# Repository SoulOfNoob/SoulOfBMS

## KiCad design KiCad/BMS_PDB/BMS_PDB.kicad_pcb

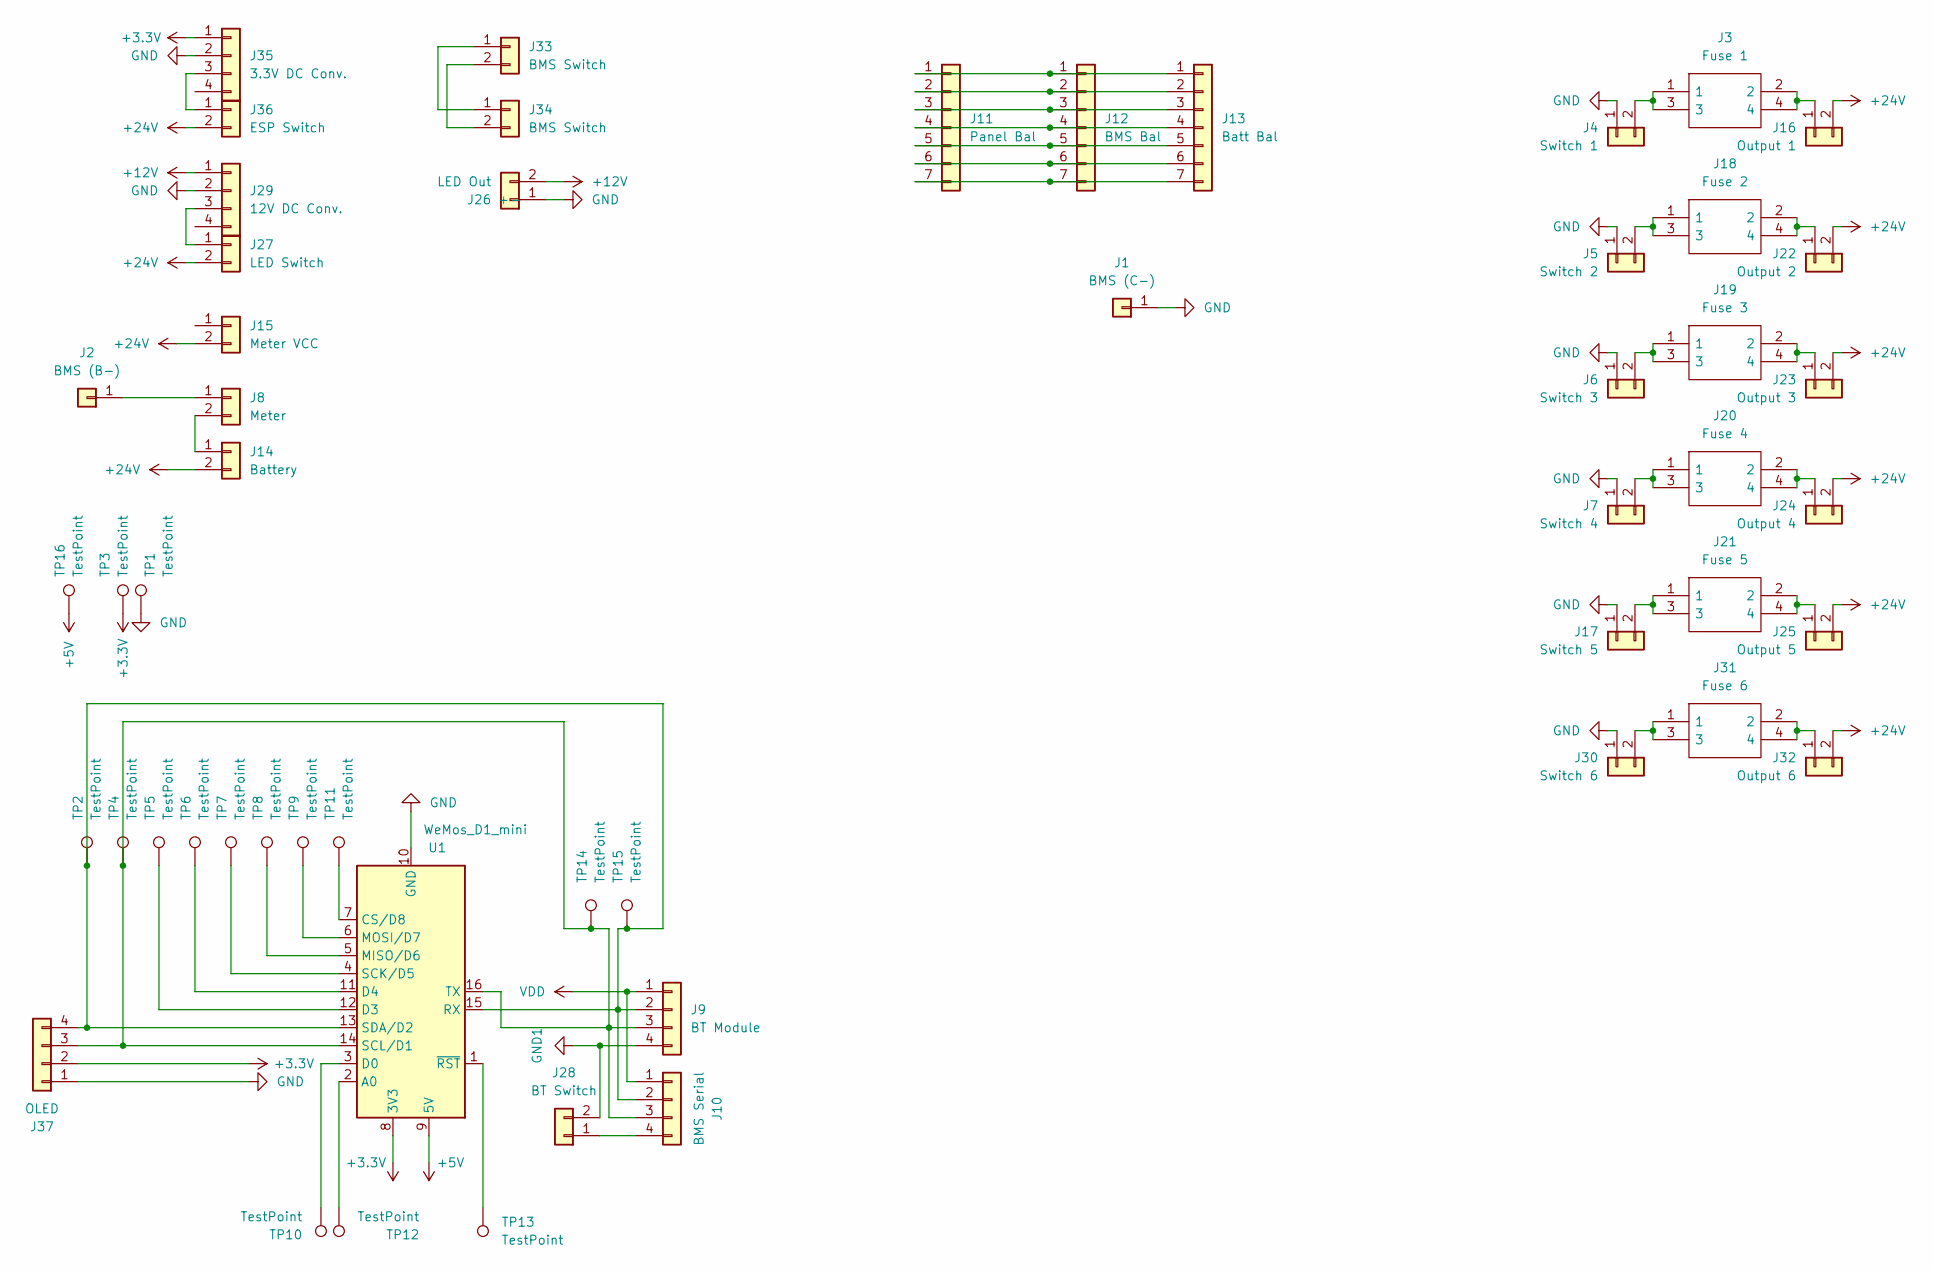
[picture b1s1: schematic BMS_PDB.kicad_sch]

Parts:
J1: BMS (C-); MountingHole_3.5mm_Pad_Via
J2: BMS (B-); MountingHole_3.5mm_Pad_Via
J3: Fuse 1; Fuseholder3557; Mouser Part Number 534-3557-2
J4: Switch 1; AMASS_XT30U-M_1x02_P5.0mm_Vertical_CUSTOM
J5: Switch 2; AMASS_XT30U-M_1x02_P5.0mm_Vertical_CUSTOM
J6: Switch 3; AMASS_XT30U-M_1x02_P5.0mm_Vertical_CUSTOM
J7: Switch 4; AMASS_XT30U-M_1x02_P5.0mm_Vertical_CUSTOM
J8: Meter; AMASS_XT60-M_1x02_P7.20mm_Vertical
J9: BT Module; JST_XH_B4B-XH-A_1x04_P2.50mm_Vertical
J10: BMS Serial; JST_XH_B4B-XH-A_1x04_P2.50mm_Vertical
J11: Panel Bal; JST_XH_B7B-XH-A_1x07_P2.50mm_Vertical
J12: BMS Bal; JST_XH_B7B-XH-A_1x07_P2.50mm_Vertical
J13: Batt Bal; JST_XH_B7B-XH-A_1x07_P2.50mm_Vertical
J14: Battery; AMASS_XT60-M_1x02_P7.20mm_Vertical
J15: Meter VCC; JST_XH_B2B-XH-A_1x02_P2.50mm_Vertical
J16: Output 1; AMASS_XT30U-M_1x02_P5.0mm_Vertical_CUSTOM
J17: Switch 5; AMASS_XT30U-M_1x02_P5.0mm_Vertical_CUSTOM
J18: Fuse 2; Fuseholder3557; Mouser Part Number 534-3557-2
J19: Fuse 3; Fuseholder3557; Mouser Part Number 534-3557-2
J20: Fuse 4; Fuseholder3557; Mouser Part Number 534-3557-2
J21: Fuse 5; Fuseholder3557; Mouser Part Number 534-3557-2
J22: Output 2; AMASS_XT30U-M_1x02_P5.0mm_Vertical_CUSTOM
J23: Output 3; AMASS_XT30U-M_1x02_P5.0mm_Vertical_CUSTOM
J24: Output 4; AMASS_XT30U-M_1x02_P5.0mm_Vertical_CUSTOM
J25: Output 5; AMASS_XT30U-M_1x02_P5.0mm_Vertical_CUSTOM
J26: LED Out; JST_XH_B2B-XH-A_1x02_P2.50mm_Vertical
J27: LED Switch; JST_XH_B2B-XH-A_1x02_P2.50mm_Vertical
J28: BT Switch; JST_XH_B2B-XH-A_1x02_P2.50mm_Vertical
J29: 12V DC Conv.; PinHeader_1x04_P2.54mm_Vertical
J30: Switch 6; AMASS_XT30U-M_1x02_P5.0mm_Vertical_CUSTOM
J31: Fuse 6; Fuseholder3557; Mouser Part Number 534-3557-2
J32: Output 6; AMASS_XT30U-M_1x02_P5.0mm_Vertical_CUSTOM
J33, J34: BMS Switch; JST_XH_B2B-XH-A_1x02_P2.50mm_Vertical
J35: 3.3V DC Conv.; PinHeader_1x04_P2.54mm_Vertical
J36: ESP Switch; JST_XH_B2B-XH-A_1x02_P2.50mm_Vertical
J37: OLED; JST_XH_B4B-XH-A_1x04_P2.50mm_Vertical
TP1, TP2, TP3, TP4, TP5, TP6, TP7, TP8, TP9, TP10, TP11, TP12, TP13, TP14, TP15, TP16: TestPoint; TestPoint_Pad_1.5x1.5mm
U1: WeMos_D1_mini; WEMOS_D1_mini_light

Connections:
+3.3V: J35.1, J37.2, TP3.1, U1.8 (3V3)
+5V: TP16.1, U1.9 (5V)
+12V: J26.2, J29.1
+24V: J14.2, J15.2, J16.2, J22.2, J23.2, J24.2, J25.2, J27.2, J32.2, J36.2
GND: J1.1, J4.1, J5.1, J6.1, J7.1, J17.1, J26.1, J29.2, J30.1, J35.2, J37.1, TP1.1, U1.10 (GND)
GND1: J9.4, J28.2
unnamed: J2.1, J8.1
unnamed: J3.1, J3.3, J4.2
unnamed: J10.4, J28.1
unnamed: J11.1, J12.1, J13.1
unnamed: J11.2, J12.2, J13.2
unnamed: J11.3, J12.3, J13.3
unnamed: J11.4, J12.4, J13.4
unnamed: J11.5, J12.5, J13.5
unnamed: J11.6, J12.6, J13.6
unnamed: J11.7, J12.7, J13.7
unnamed: J8.2, J14.1
unnamed: J3.2, J3.4, J16.1
unnamed: J17.2, J21.1, J21.3
unnamed: J5.2, J18.1, J18.3
unnamed: J18.2, J18.4, J22.1
unnamed: J6.2, J19.1, J19.3
unnamed: J19.2, J19.4, J23.1
unnamed: J7.2, J20.1, J20.3
unnamed: J20.2, J20.4, J24.1
unnamed: J21.2, J21.4, J25.1
unnamed: J27.1, J29.3
unnamed: J30.2, J31.1, J31.3
unnamed: J31.2, J31.4, J32.1
unnamed: J33.1, J34.1
unnamed: J33.2, J34.2
unnamed: J35.3, J36.1
unnamed: J9.3, J10.3, J37.3, TP4.1, TP14.1, U1.14 (SCL/D1), U1.16 (TX)
unnamed: J9.2, J10.2, J37.4, TP2.1, TP15.1, U1.13 (SDA/D2), U1.15 (RX)
unnamed: TP5.1, U1.12 (D3)
unnamed: TP6.1, U1.11 (D4)
unnamed: TP7.1, U1.4 (SCK/D5)
unnamed: TP8.1, U1.5 (MISO/D6)
unnamed: TP9.1, U1.6 (MOSI/D7)
unnamed: TP10.1, U1.3 (D0)
unnamed: TP11.1, U1.7 (CS/D8)
unnamed: TP12.1, U1.2 (A0)
unnamed: TP13.1, U1.1 (~RST)
VDD: J9.1, J10.1

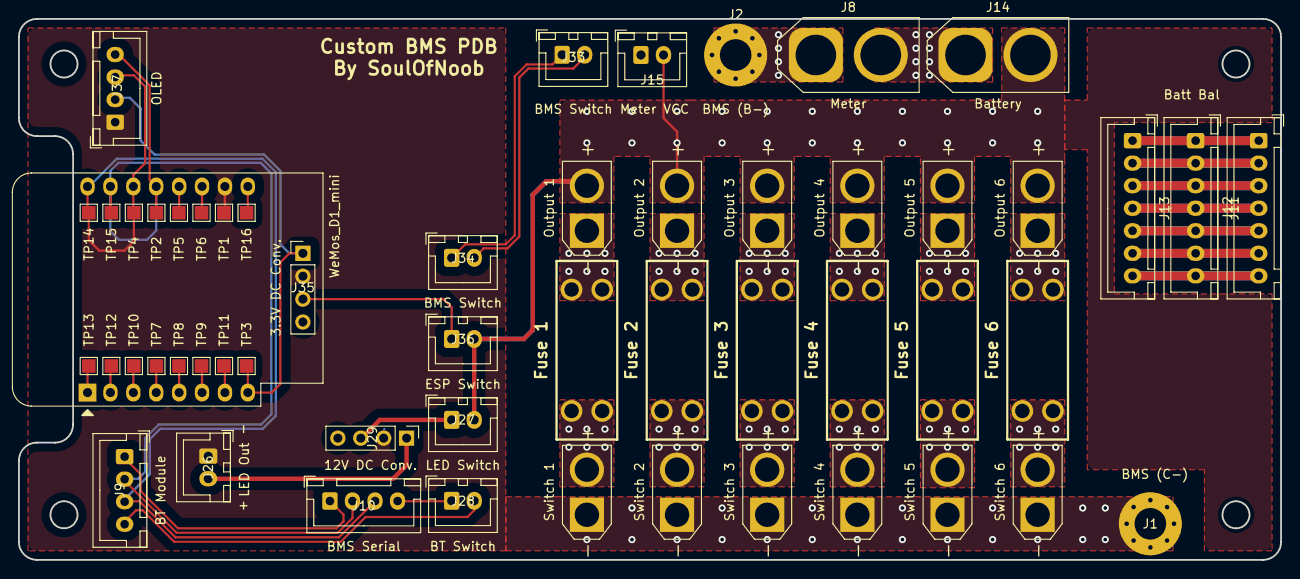
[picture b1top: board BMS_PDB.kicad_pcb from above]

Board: 2 copper layers, 140.0 x 60.0 mm, 54 parts (0 on the bottom side), 44 nets.

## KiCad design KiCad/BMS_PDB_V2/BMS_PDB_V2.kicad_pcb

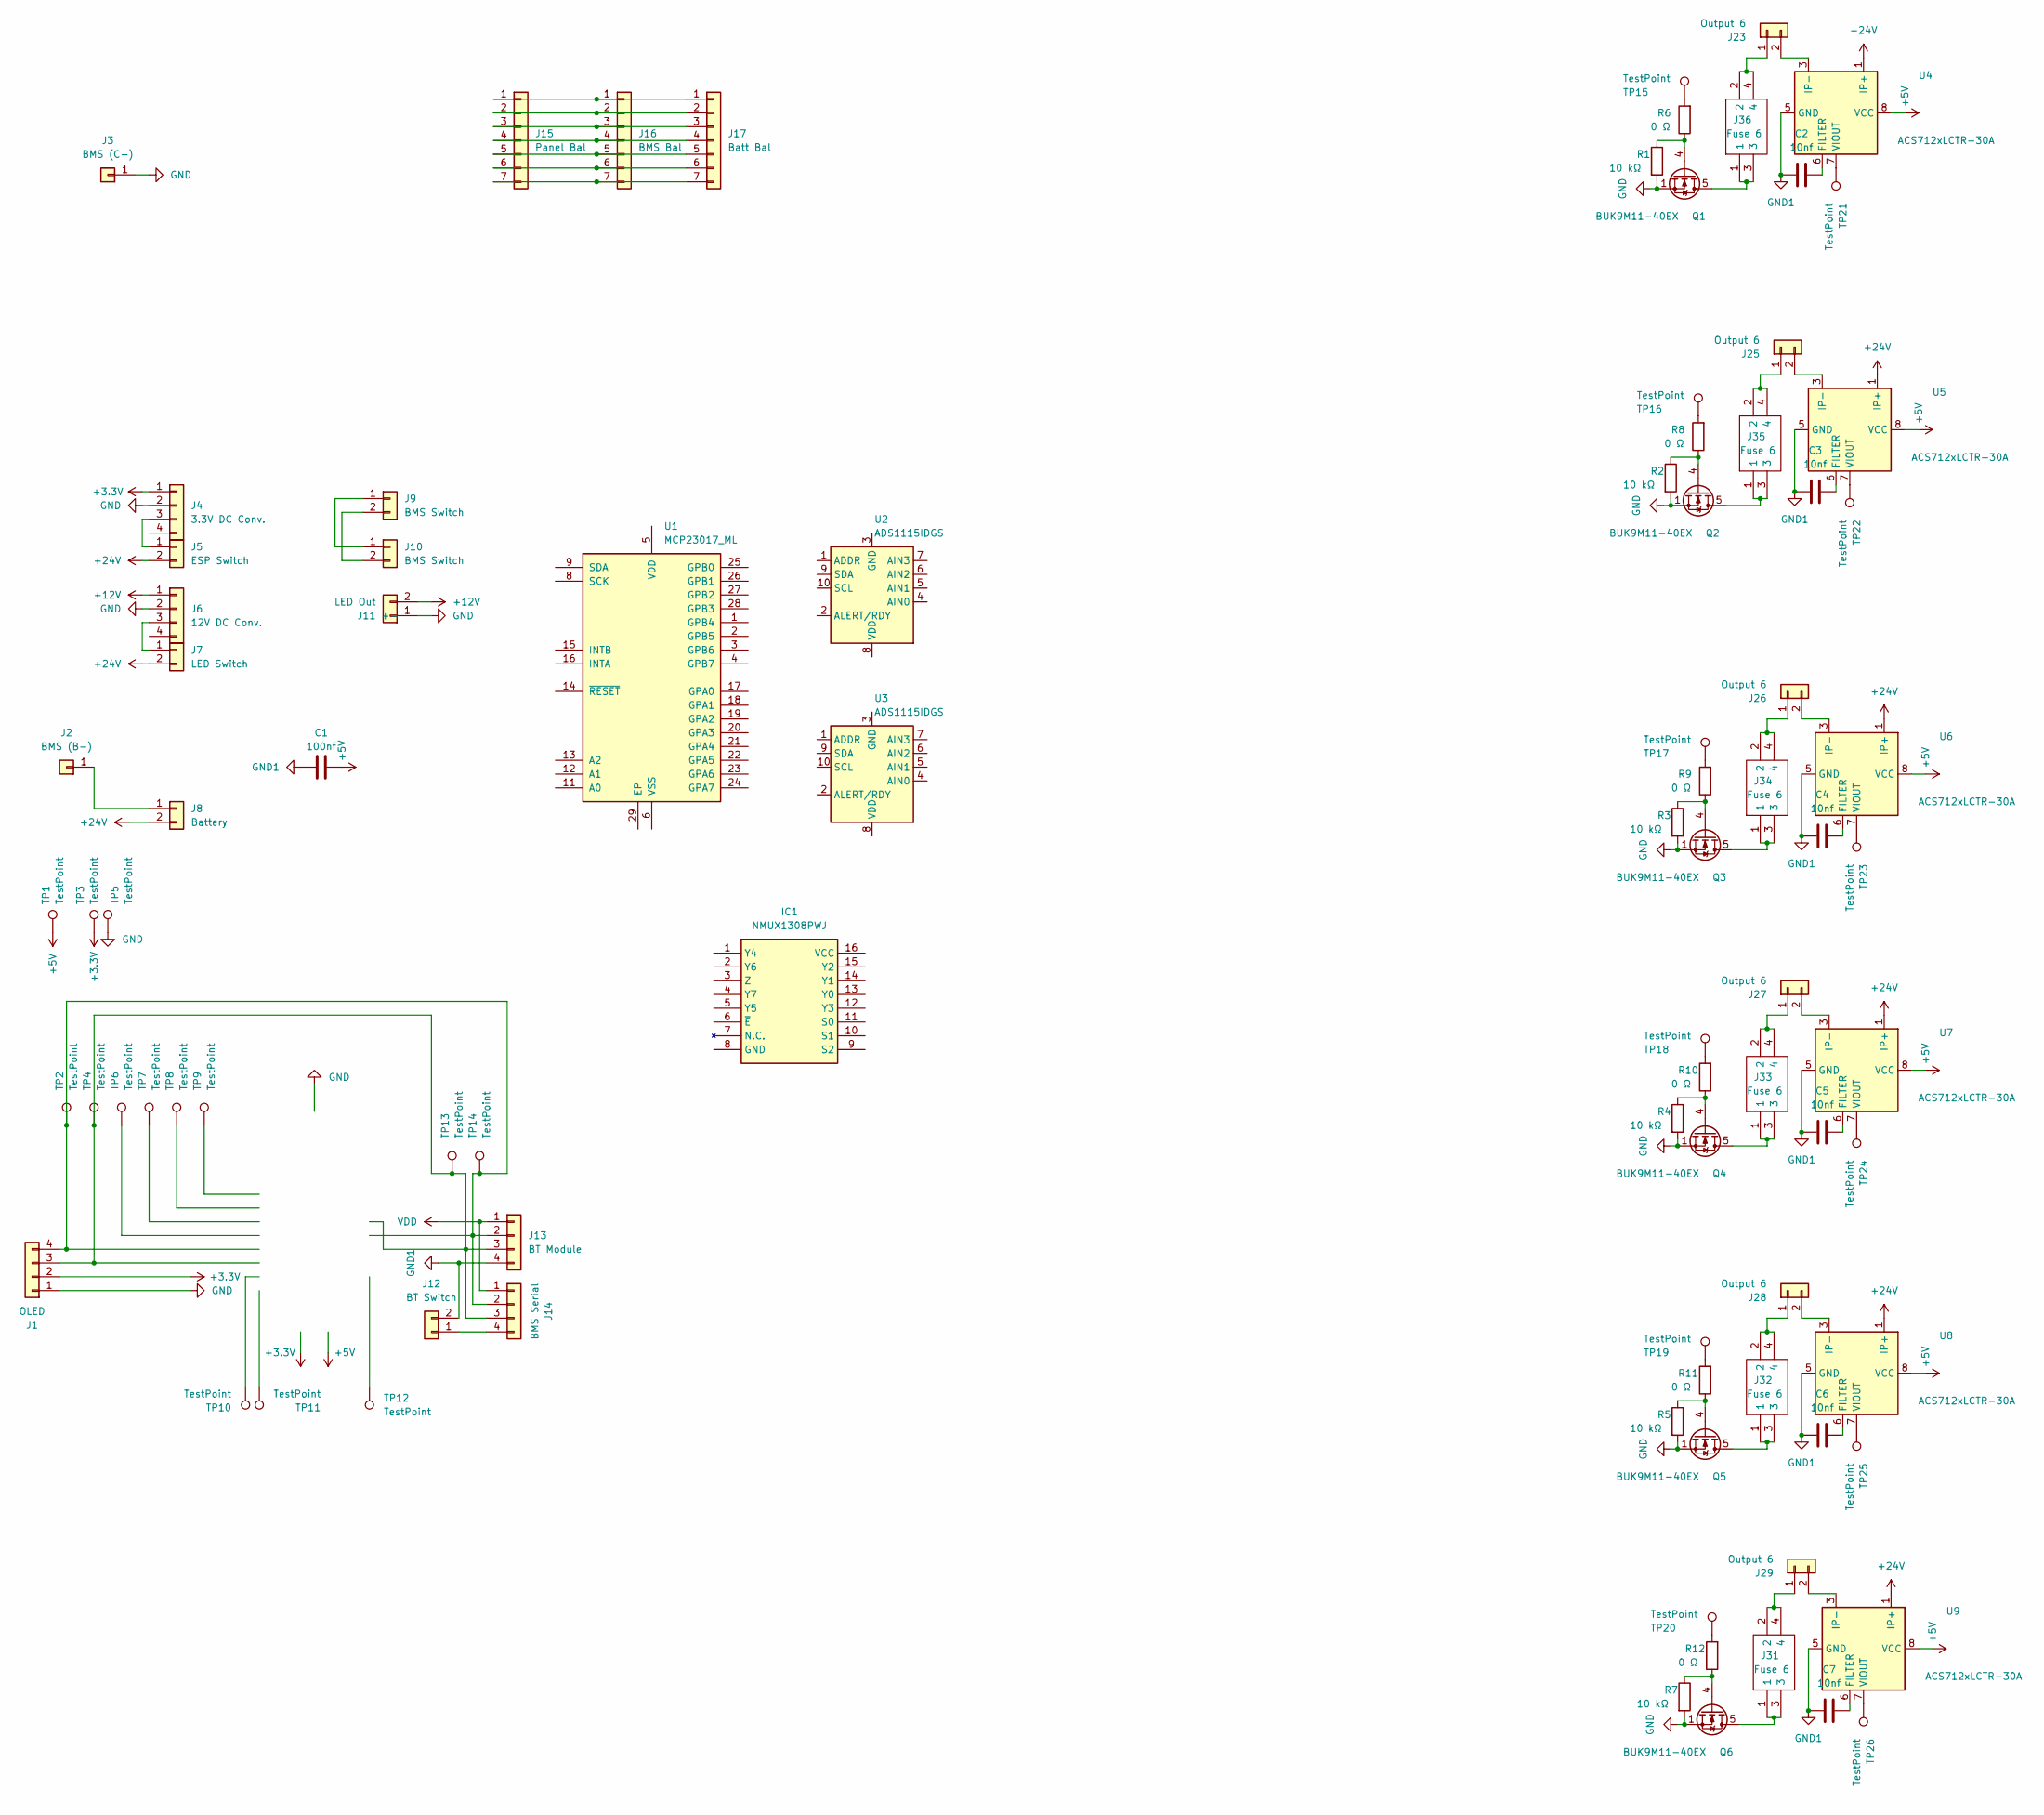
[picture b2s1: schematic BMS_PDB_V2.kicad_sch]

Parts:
C1: 100nf; R_0603_1608Metric
C2, C3, C4, C5, C6, C7: 10nf; R_0603_1608Metric
IC1: NMUX1308PWJ; Manufacturer_Part_Number NMUX1308PWJ
J1: OLED; JST_XH_B4B-XH-A_1x04_P2.50mm_Vertical
J2: BMS (B-); MountingHole_3.5mm_Pad_Via
J3: BMS (C-); MountingHole_3.5mm_Pad_Via
J4: 3.3V DC Conv.; PinHeader_1x04_P2.54mm_Vertical
J5: ESP Switch; JST_XH_B2B-XH-A_1x02_P2.50mm_Vertical
J6: 12V DC Conv.; PinHeader_1x04_P2.54mm_Vertical
J7: LED Switch; JST_XH_B2B-XH-A_1x02_P2.50mm_Vertical
J8: Battery; AMASS_XT60-M_1x02_P7.20mm_Vertical
J9, J10: BMS Switch; JST_XH_B2B-XH-A_1x02_P2.50mm_Vertical
J11: LED Out; JST_XH_B2B-XH-A_1x02_P2.50mm_Vertical
J12: BT Switch; JST_XH_B2B-XH-A_1x02_P2.50mm_Vertical
J13: BT Module; JST_XH_B4B-XH-A_1x04_P2.50mm_Vertical
J14: BMS Serial; JST_XH_B4B-XH-A_1x04_P2.50mm_Vertical
J15: Panel Bal; JST_XH_B7B-XH-A_1x07_P2.50mm_Vertical
J16: BMS Bal; JST_XH_B7B-XH-A_1x07_P2.50mm_Vertical
J17: Batt Bal; JST_XH_B7B-XH-A_1x07_P2.50mm_Vertical
J23, J25, J26, J27, J28, J29: Output 6; AMASS_XT30U-M_1x02_P5.0mm_Vertical
J31, J32, J33, J34, J35, J36: Fuse 6; Fuseholder3557; Mouser Part Number 534-3557-2
Q1, Q2, Q3, Q4, Q5, Q6: BUK9M11-40EX; LFPAK33
R1, R2, R3, R4, R5, R7: 10 kΩ; R_0402_1005Metric
R6, R8, R9, R10, R11, R12: 0 Ω; R_0402_1005Metric
TP1, TP2, TP3, TP4, TP5, TP6, TP7, TP8, TP9, TP10, TP11, TP12, TP13, TP14, TP15, TP16, TP17, TP18, TP19, TP20, TP21, TP22, TP23, TP24, TP25, TP26: TestPoint; TestPoint_Pad_1.5x1.5mm
U1: MCP23017_ML; QFN-28-1EP_6x6mm_P0.65mm_EP4.25x4.25mm
U2, U3: ADS1115IDGS; TSSOP-10_3x3mm_P0.5mm
U4, U5, U6, U7, U8, U9: ACS712xLCTR-30A; SOIC-8_3.9x4.9mm_P1.27mm

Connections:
+3.3V: J1.2, J4.1, TP3.1
+5V: C1.2, TP1.1, U4.8 (VCC), U5.8 (VCC), U6.8 (VCC), U7.8 (VCC), U8.8 (VCC), U9.8 (VCC)
+12V: J6.1, J11.2
+24V: J5.2, J7.2, J8.2, U4.1 (IP+), U4.2 (IP+), U5.1 (IP+), U5.2 (IP+), U6.1 (IP+), U6.2 (IP+), U7.1 (IP+), U7.2 (IP+), U8.1 (IP+), U8.2 (IP+), U9.1 (IP+), U9.2 (IP+)
GND: J1.1, J3.1, J4.2, J6.2, J11.1, Q1.1 (S), Q1.2 (S), Q1.3 (S), Q2.1 (S), Q2.2 (S), Q2.3 (S), Q3.1 (S), Q3.2 (S), Q3.3 (S), Q4.1 (S), Q4.2 (S), Q4.3 (S), Q5.1 (S), Q5.2 (S), Q5.3 (S), Q6.1 (S), Q6.2 (S), Q6.3 (S), R1.2, R2.2, R3.2, R4.2, R5.2, R7.2, TP5.1
GND1: C1.1, C2.1, C3.1, C4.1, C5.1, C6.1, C7.1, J12.2, J13.4, U4.5 (GND), U5.5 (GND), U6.5 (GND), U7.5 (GND), U8.5 (GND), U9.5 (GND)
unnamed: J1.3, J13.3, J14.3, TP4.1, TP13.1
unnamed: J1.4, J13.2, J14.2, TP2.1, TP14.1
unnamed: J2.1, J8.1
unnamed: J4.3, J5.1
unnamed: J6.3, J7.1
unnamed: J9.1, J10.1
unnamed: J9.2, J10.2
unnamed: J12.1, J14.4
unnamed: J15.1, J16.1, J17.1
unnamed: J15.2, J16.2, J17.2
unnamed: J15.3, J16.3, J17.3
unnamed: J15.4, J16.4, J17.4
unnamed: J15.5, J16.5, J17.5
unnamed: J15.6, J16.6, J17.6
unnamed: J15.7, J16.7, J17.7
unnamed: J23.1, J36.2, J36.4
unnamed: J23.2, U4.3 (IP-), U4.4 (IP-)
unnamed: J25.1, J35.2, J35.4
unnamed: J25.2, U5.3 (IP-), U5.4 (IP-)
unnamed: J26.1, J34.2, J34.4
unnamed: J26.2, U6.3 (IP-), U6.4 (IP-)
unnamed: J27.1, J33.2, J33.4
unnamed: J27.2, U7.3 (IP-), U7.4 (IP-)
unnamed: J28.1, J32.2, J32.4
unnamed: J28.2, U8.3 (IP-), U8.4 (IP-)
unnamed: J29.1, J31.2, J31.4
unnamed: J29.2, U9.3 (IP-), U9.4 (IP-)
unnamed: J36.1, J36.3, Q1.5 (D)
unnamed: Q1.4 (G), R1.1, R6.1
unnamed: J35.1, J35.3, Q2.5 (D)
unnamed: Q2.4 (G), R2.1, R8.1
unnamed: J34.1, J34.3, Q3.5 (D)
unnamed: Q3.4 (G), R3.1, R9.1
unnamed: J33.1, J33.3, Q4.5 (D)
unnamed: Q4.4 (G), R4.1, R10.1
unnamed: J32.1, J32.3, Q5.5 (D)
unnamed: Q5.4 (G), R5.1, R11.1
unnamed: J31.1, J31.3, Q6.5 (D)
unnamed: Q6.4 (G), R7.1, R12.1
unnamed: R6.2, TP15.1
unnamed: R8.2, TP16.1
unnamed: R9.2, TP17.1
unnamed: R10.2, TP18.1
unnamed: R11.2, TP19.1
unnamed: R12.2, TP20.1
unnamed: C2.2, U4.6 (FILTER)
unnamed: TP21.1, U4.7 (VIOUT)
unnamed: C3.2, U5.6 (FILTER)
unnamed: TP22.1, U5.7 (VIOUT)
unnamed: C4.2, U6.6 (FILTER)
unnamed: TP23.1, U6.7 (VIOUT)
unnamed: C5.2, U7.6 (FILTER)
unnamed: TP24.1, U7.7 (VIOUT)
unnamed: C6.2, U8.6 (FILTER)
unnamed: TP25.1, U8.7 (VIOUT)
unnamed: C7.2, U9.6 (FILTER)
unnamed: TP26.1, U9.7 (VIOUT)
VDD: J13.1, J14.1

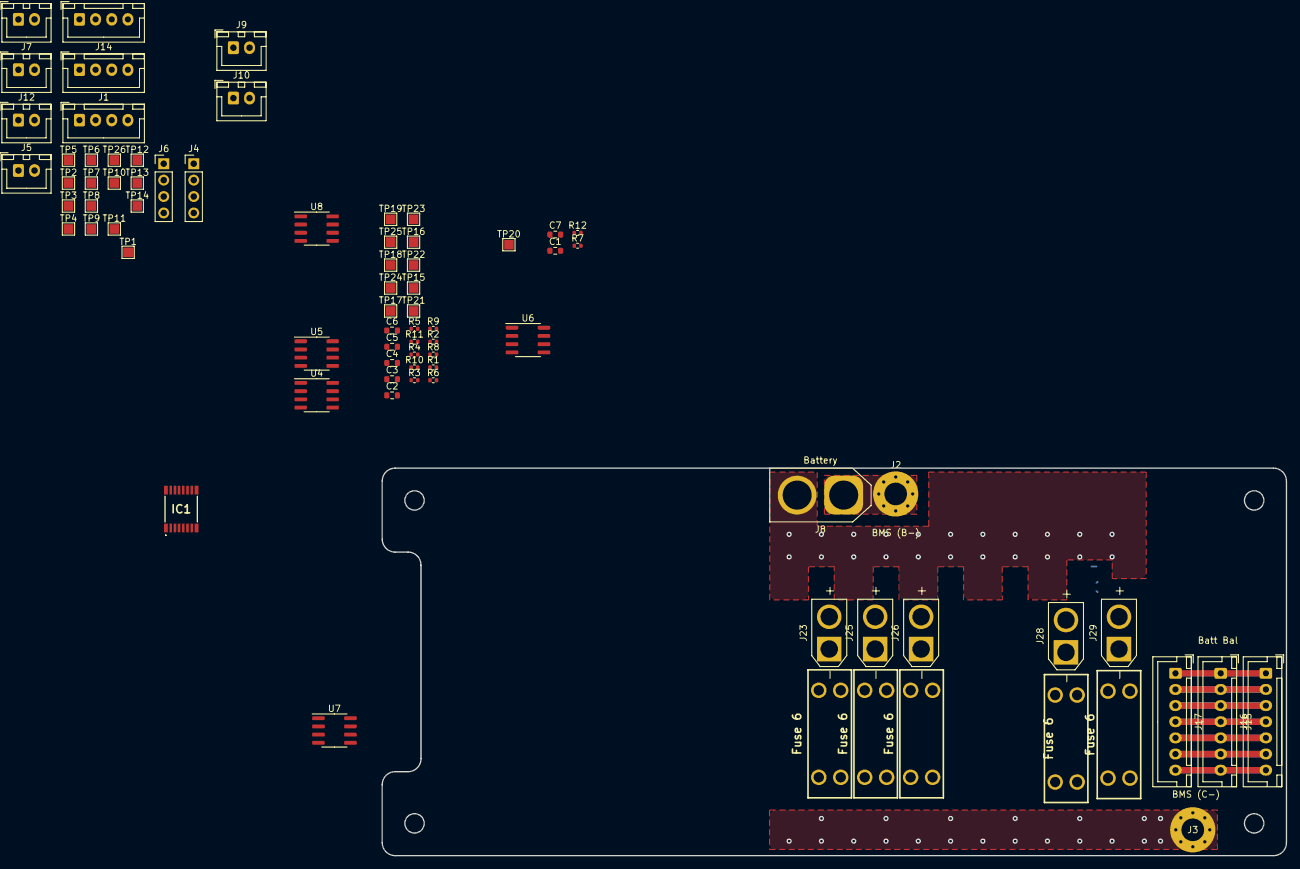
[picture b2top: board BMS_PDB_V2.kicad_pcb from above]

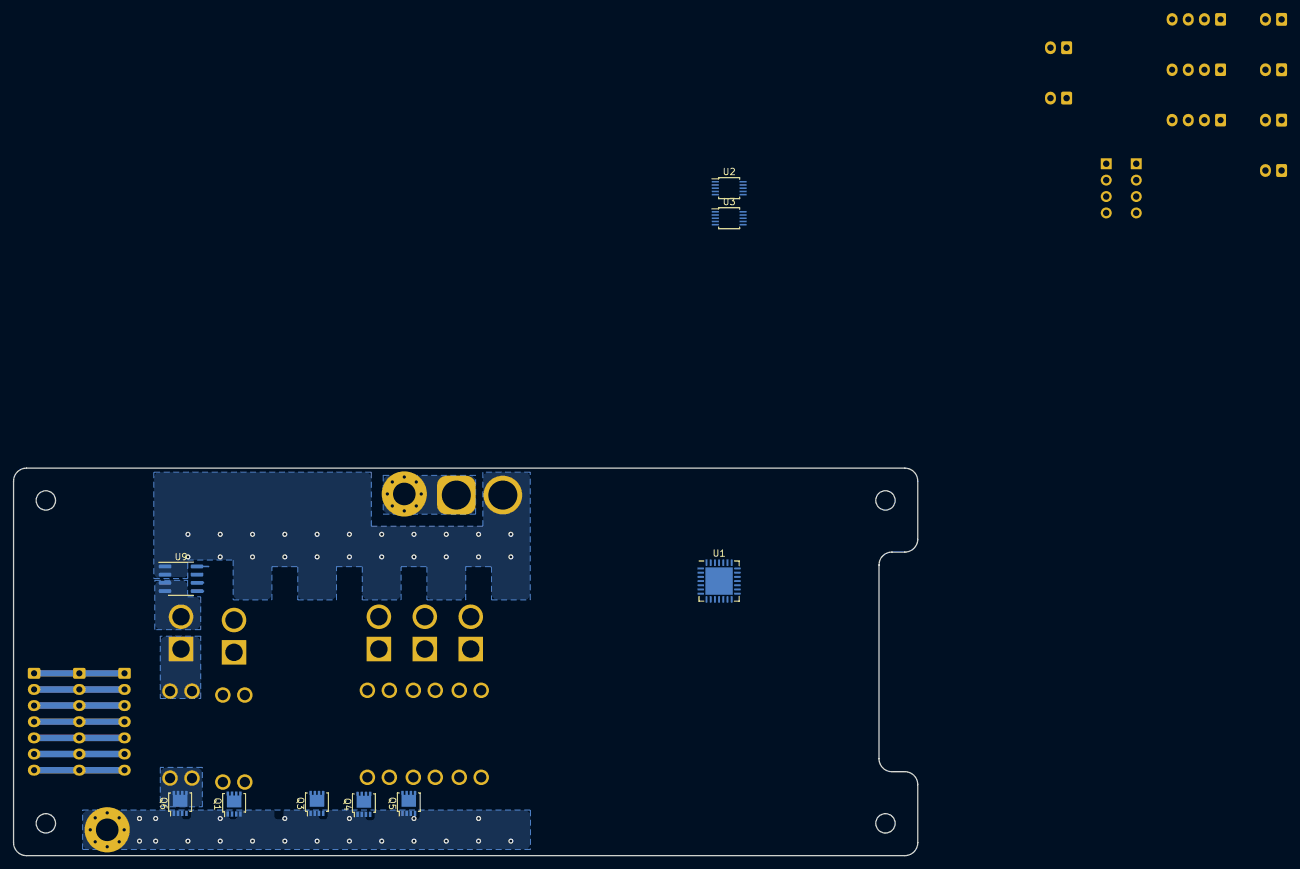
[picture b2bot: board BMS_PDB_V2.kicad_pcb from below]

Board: 2 copper layers, 140.0 x 60.0 mm, 87 parts (9 on the bottom side), 62 nets.

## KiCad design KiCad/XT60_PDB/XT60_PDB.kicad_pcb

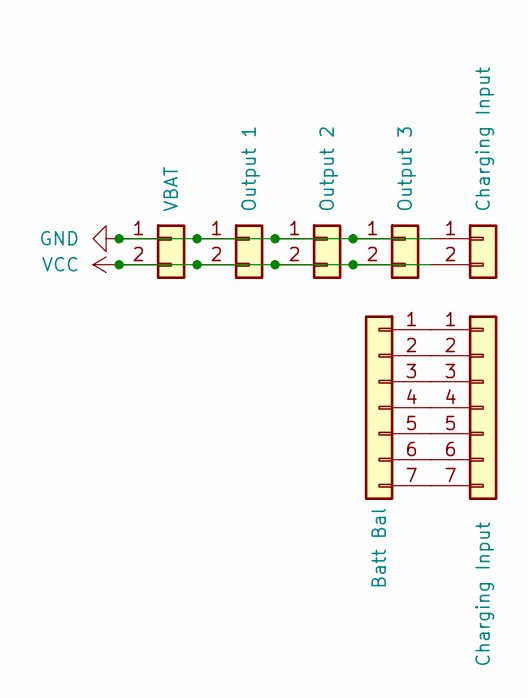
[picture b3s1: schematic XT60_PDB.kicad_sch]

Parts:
J1: VBAT; AMASS_XT30PW-M_1x02_P2.50mm_Horizontal
J2: Output 1; AMASS_XT60-M_1x02_P7.20mm_Vertical
J3: Output 2; AMASS_XT60-M_1x02_P7.20mm_Vertical
J4: Batt Bal; JST_XH_S7B-XH-A_1x07_P2.50mm_Horizontal
J5: Output 3; AMASS_XT60-M_1x02_P7.20mm_Vertical
J6: Charging Input; AMASS_XT60-M_1x02_P7.20mm_Vertical
J7: Charging Input; JST_XH_B7B-XH-A_1x07_P2.50mm_Vertical

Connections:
GND: J1.1, J2.1, J3.1, J5.1, J6.1
unnamed: J4.1, J7.1
unnamed: J4.2, J7.2
unnamed: J4.3, J7.3
unnamed: J4.4, J7.4
unnamed: J4.5, J7.5
unnamed: J4.6, J7.6
unnamed: J4.7, J7.7
VCC: J1.2, J2.2, J3.2, J5.2, J6.2

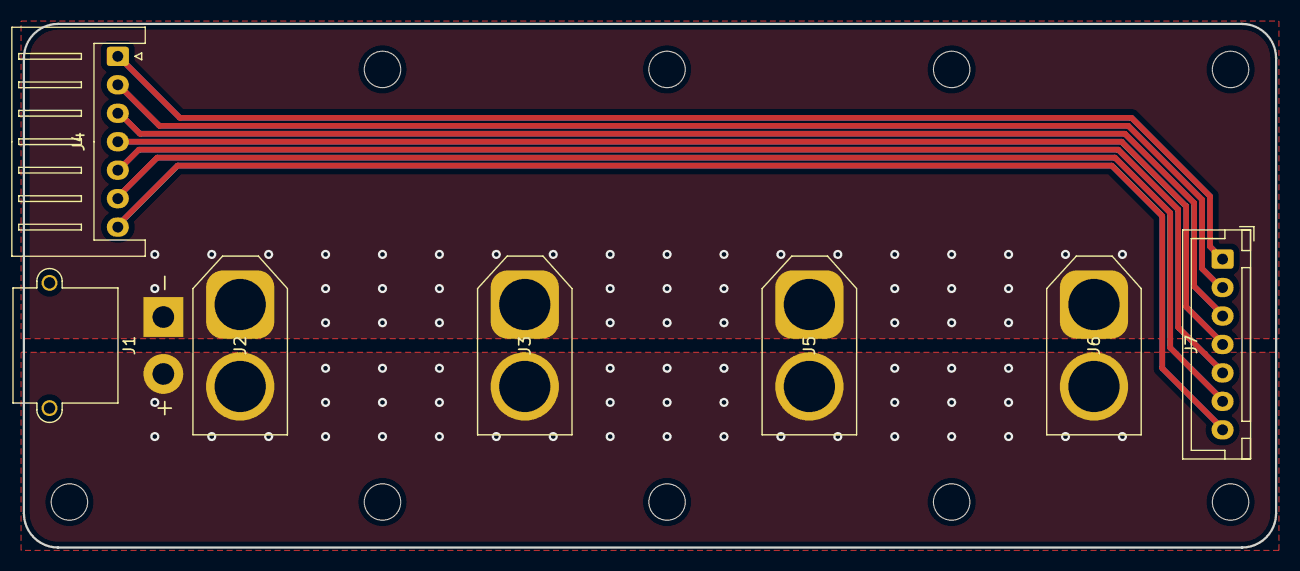
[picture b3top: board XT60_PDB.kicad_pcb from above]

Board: 2 copper layers, 110.0 x 46.0 mm, 7 parts (0 on the bottom side), 9 nets.

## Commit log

2023-04-17 add charging indicator
2023-04-17 rip out stream reference from lib
2023-04-17 add ePaper
2023-04-20 add RTC and SD
2023-04-20 add pico and todos
2023-04-20 exclude rtc
2023-04-21 Major refactor
2023-04-23 Integrade Bluetooth passthrough
2023-04-23 working prototype
2023-04-23 change prio
2023-04-24 add capacity to display
2023-04-24 define states
2023-04-24 add states
2023-05-10 bottelon state
2023-06-19 defqon label
2024-02-12 add KiCad Files
2024-02-12 somechanges
2024-06-08 fix: fix remaining hours calculation
2024-06-08 move serial print to logger and fix Wh calculations
2024-06-08 thin out logging
2024-06-08 fix: cleanup serial prints
2024-06-08 refactor: remove helper
2024-06-08 feature: reduce esp32 clock speed
2024-06-08 refactor: remove helper class
2024-06-08 refactor: change BLE name
2024-06-08 feature: clean up display
2024-06-08 fix: 20mhz is supported
2024-06-08 refactor: change naming of foreign task name
2024-06-08 bt only works on 80mhz
2024-06-08 don't reboot on BT
2024-06-08 reboot every 10 minutes to avoid ble issues
2024-06-23 update libs
2024-06-23 add bt swtich, disable reboot and partial refresh for defqon
2024-06-23 disable OLED and logging when lid is closed
2024-06-23 feat: implement deep sleep when lid is closed and BT is off, soft restart when bt is enabled
2024-06-23 only refresh epaper on hard reset
2024-06-23 add voltage reading for internal battery
2024-06-25 refactor and fix idf version so BT keeps working
2024-06-25 refactor display and bt connection
2024-06-25 redundant code in bt
2024-06-25 fix: speedup boot time
